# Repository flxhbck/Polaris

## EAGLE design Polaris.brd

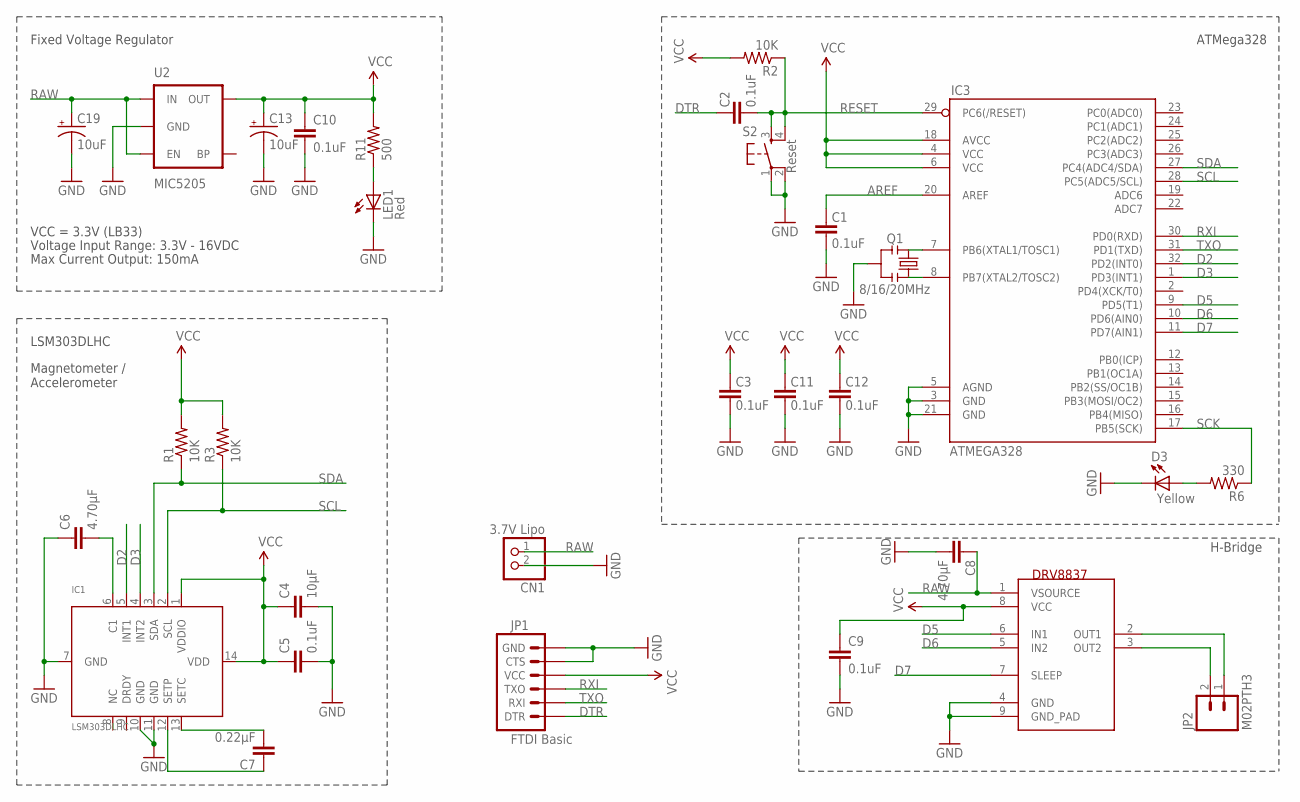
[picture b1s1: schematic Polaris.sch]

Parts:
C1, C2, C3, C5, C9, C10, C11, C12: 0.1uF; 0805
C4: 10µF; 0805
C6, C8: 4.70µF; 0805
C7: 0.22µF; 0805
C13, C19: 10uF; EIA3216
CN1: 3.7V Lipo; JST-PH-2-THM-RA
D3: Yellow; LED-1206
IC1: LSM303DLHC; LGA14
IC2: DRV8837; WSON-8
IC3: ATMEGA328; TQFP32-08
JP1: FTDI Basic; 1X06
JP2: M02PTH3; 1X02_LONGPADS
LED1: Red; LED-1206
Q1: 8/16/20MHz; RESONATOR-SMD
R1, R2, R3: 10K; 0805
R6: 330; 0805
R11: 500; 0805
S2: Reset; TACTILE_SWITCH_SMD
U2: MIC5205; SOT23-5

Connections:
3.3V: C3.2, C4.1, C5.1, C9.1, C10.1, C11.2, C12.2, C13.A (+), IC1.1 (VDDIO), IC1.14 (VDD), IC2.8 (VCC), IC3.4 (VCC), IC3.6 (VCC), IC3.18 (AVCC), JP1.4 (VCC), R1.2, R2.2, R3.2, R11.2, U2.5 (OUT)
AREF: C1.2, IC3.20 (AREF)
D2: IC1.5 (INT1), IC3.32 (PD2(INT0))
D3: IC1.4 (INT2), IC3.1 (PD3(INT1))
D5: IC2.6 (IN1), IC3.9 (PD5(T1))
D6: IC2.5 (IN2), IC3.10 (PD6(AIN0))
D7: IC2.7 (SLEEP), IC3.11 (PD7(AIN1))
DTR: C2.2, JP1.1 (DTR)
GND: C1.1, C3.1, C4.2, C5.2, C6.1, C8.2, C9.2, C10.2, C11.1, C12.1, C13.C (-), C19.C (-), CN1.2 (1), D3.C, IC1.7 (GND), IC1.10 (GND), IC1.11 (GND), IC2.4 (GND), IC2.9 (GND_PAD), IC3.3 (GND), IC3.5 (AGND), IC3.21 (GND), JP1.5 (CTS), JP1.6 (GND), LED1.C, Q1.2, S2.1, S2.2, U2.2 (GND)
unnamed: IC3.8 (PB7(XTAL2/TOSC2)), Q1.1
unnamed: IC3.7 (PB6(XTAL1/TOSC1)), Q1.3
unnamed: C6.2, IC1.6 (C1)
unnamed: C7.1, IC1.12 (SETP)
unnamed: C7.2, IC1.13 (SETC)
unnamed: D3.A, R6.2
unnamed: IC2.3 (OUT2), JP2.2
unnamed: IC2.2 (OUT1), JP2.1
unnamed: LED1.A, R11.1
RAW: C8.1, C19.A (+), CN1.1 (2), IC2.1 (VSOURCE), U2.1 (IN), U2.3 (EN)
RESET: C2.1, IC3.29 (PC6(/RESET)), R2.1, S2.3, S2.4
RXI: IC3.30 (PD0(RXD)), JP1.3 (TXO)
SCK: IC3.17 (PB5(SCK)), R6.1
SCL: IC1.2 (SCL), IC3.28 (PC5(ADC5/SCL)), R3.1
SDA: IC1.3 (SDA), IC3.27 (PC4(ADC4/SDA)), R1.1
TXO: IC3.31 (PD1(TXD)), JP1.2 (RXI)

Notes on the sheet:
Max Current Output: 150mA
VCC = 3.3V (LB33)
Voltage Input Range: 3.3V - 16VDC
LSM303DLHC
Magnetometer / Accelerometer
H-Bridge
Fixed Voltage Regulator
ATMega328

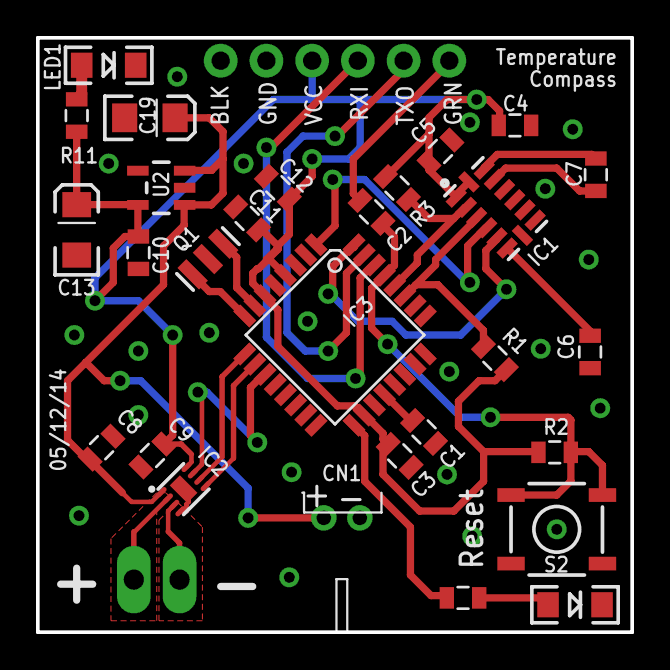
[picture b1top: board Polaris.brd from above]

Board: 2 copper layers, 33.0 x 33.0 mm, 30 parts (1 on the bottom side), 25 nets.

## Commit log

2015-02-18 create

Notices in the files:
parts and their libraries:
microbuilder: This work is placed in the public domain, and may be freely used for commercial and non-commercial work with the following conditions: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
SparkFun-Connectors: Licensing: CC v3.0 Share-Alike You are welcome to use this library for commercial purposes.
